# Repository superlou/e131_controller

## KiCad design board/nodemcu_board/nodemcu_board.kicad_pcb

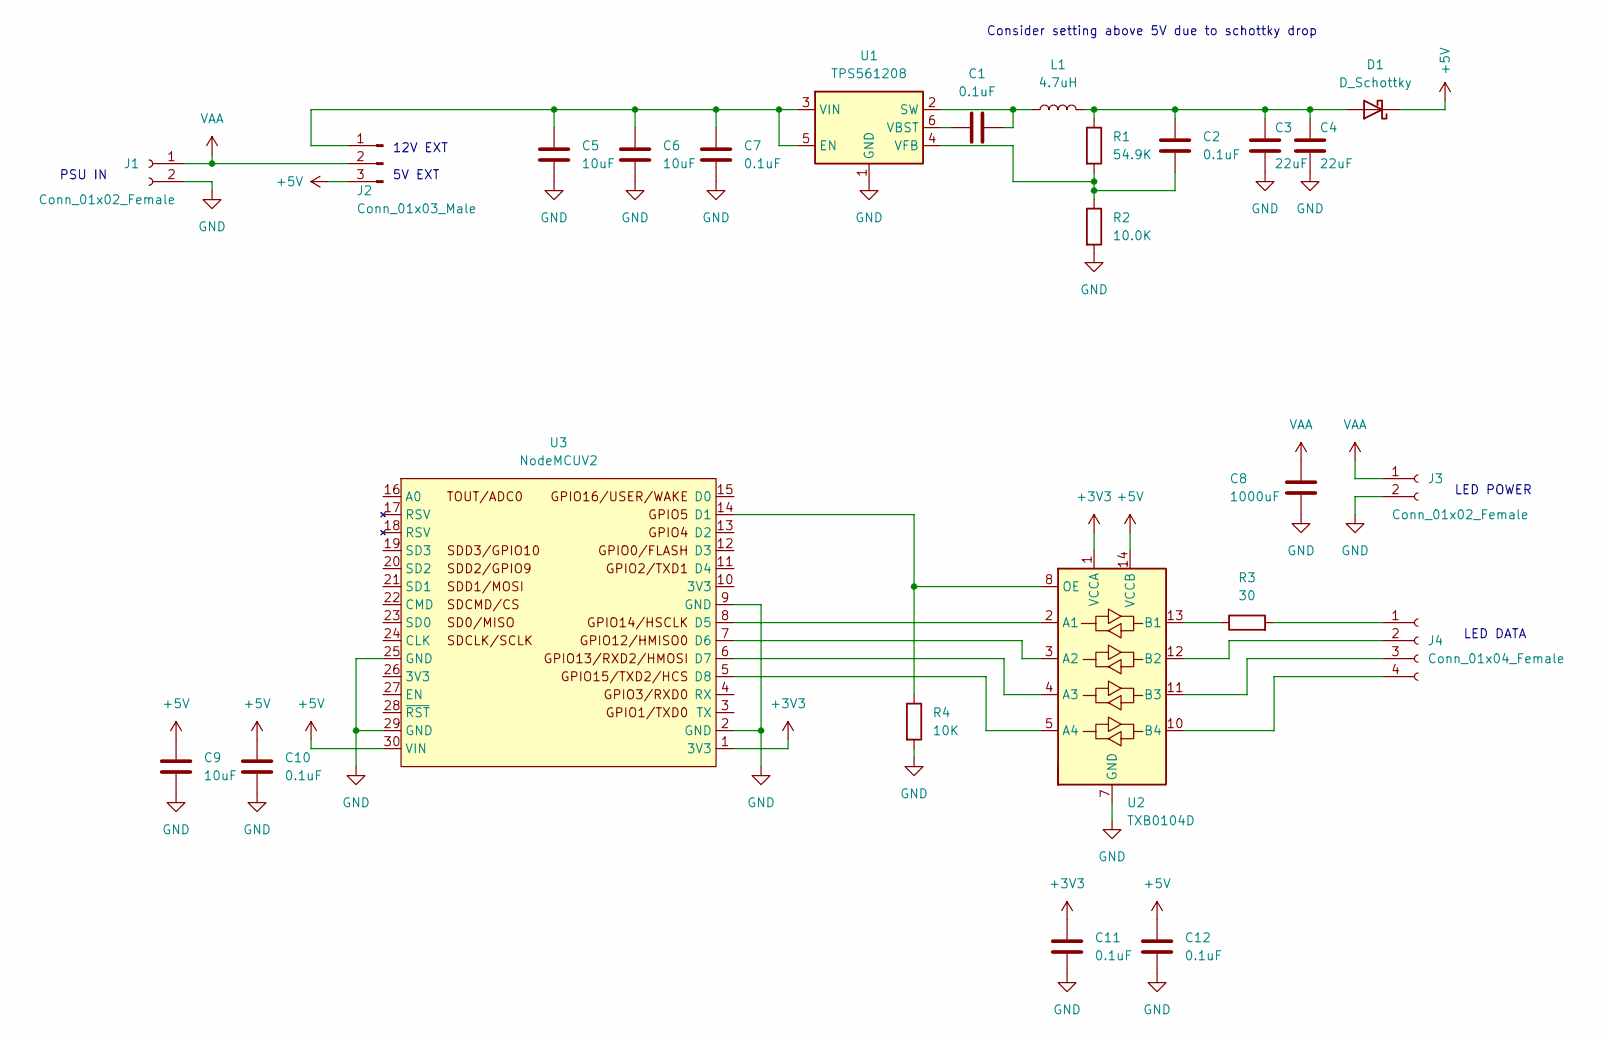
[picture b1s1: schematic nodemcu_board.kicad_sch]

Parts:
C1, C2, C7, C10, C11, C12: 0.1uF; C_0805_2012Metric
C3, C4: 22uF; C_1210_3225Metric
C5, C6, C9: 10uF; C_1210_3225Metric
C8: 1000uF; C_Radial_D8.0mm_H11.5mm_P3.50mm
D1: D_Schottky
J1, J3: Conn_01x02_Female; PinSocket_1x02_P2.54mm_Vertical
J2: Conn_01x03_Male; PinHeader_1x03_P2.54mm_Vertical
J4: Conn_01x04_Female; PinHeader_1x04_P2.54mm_Vertical
L1: 4.7uH
R1: 54.9K; R_0805_2012Metric
R2: 10.0K; R_0805_2012Metric
R3: 30; R_0805_2012Metric
R4: 10K; R_0805_2012Metric
U1: TPS561208; SOT-23-6
U2: TXB0104D; SOIC-14_3.9x8.7mm_P1.27mm
U3: NodeMCUV2; nodemcu_v2

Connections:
+3V3: C11.1, U2.1 (VCCA), U3.1 (3V3)
+5V: C9.1, C10.1, C12.1, D1.1 (K), J2.3, U2.14 (VCCB), U3.30 (VIN)
GND: C3.2, C4.2, C5.2, C6.2, C7.2, C8.2, C9.2, C10.2, C11.2, C12.2, J1.2, J3.2, R2.2, R4.2, U1.1 (GND), U2.7 (GND), U3.2 (GND), U3.9 (GND), U3.25 (GND), U3.29 (GND)
unnamed: C1.1, U1.6 (VBST)
unnamed: C1.2, L1.1, U1.2 (SW)
unnamed: C2.1, R1.2, R2.1, U1.4 (VFB)
unnamed: C2.2, C3.1, C4.1, D1.2 (A), L1.2, R1.1
unnamed: C5.1, C6.1, C7.1, J2.1, U1.3 (VIN), U1.5 (EN)
unnamed: J4.1, R3.2
unnamed: J4.2, U2.12 (B2)
unnamed: J4.3, U2.11 (B3)
unnamed: J4.4, U2.10 (B4)
unnamed: R3.1, U2.13 (B1)
unnamed: R4.1, U2.8 (OE), U3.14 (D1)
unnamed: U2.2 (A1), U3.8 (D5)
unnamed: U2.3 (A2), U3.7 (D6)
unnamed: U2.4 (A3), U3.6 (D7)
unnamed: U2.5 (A4), U3.5 (D8)
VAA: C8.1, J1.1, J2.2, J3.1

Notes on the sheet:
Consider setting above 5V due to schottky drop
12V EXT
5V EXT
LED DATA
LED POWER
PSU IN

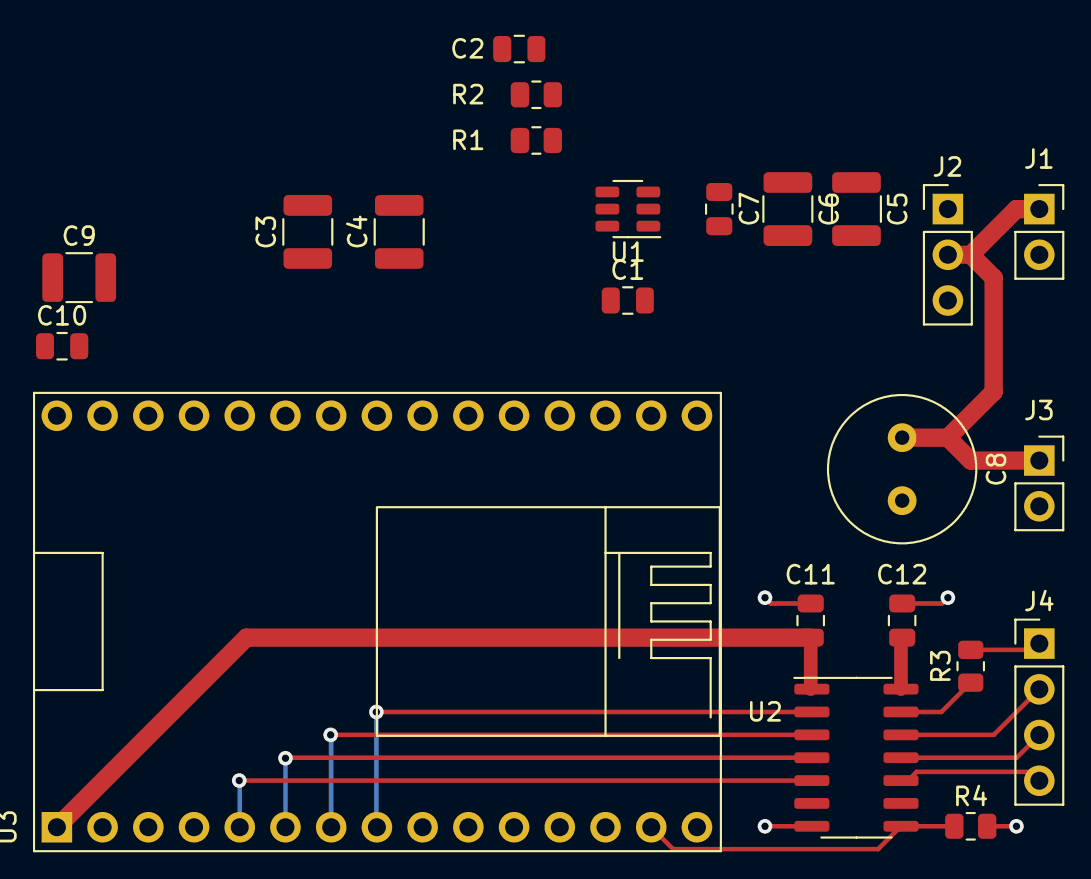
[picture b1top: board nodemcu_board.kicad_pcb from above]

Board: 2 copper layers, 23 parts (0 on the bottom side), 19 nets.

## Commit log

2025-01-02 Added config server
2025-01-05 Added wiring documentation
